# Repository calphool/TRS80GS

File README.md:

# TRS80GS
Storage area for my TRS-80 Model 1 Graphics, Sound, Gaming, and Communication cartidge

My friend's first computer was a 1977 TRS-80 Model 1.  I'm a few years younger than him, so my first computer was a TI-99/4A, 
followed soon after by an Atari 8-bit (800XL I believe).

For some reason my friend kept trying to assert that his *Trash-80* was in some way superior to all home computers of the era, 
and of course this couldn't stand.  I decided to see what all his fussing was about.  I learned some Z80 assembler, 
started hacking a TRS-80 emulator, and eventually got somewhat comfortable with Z80 assembler (I still prefer 6502 assembler).  I 
tried to do some graphics stuff, but *man*, TRS-80 Model 1's *barely* have the ability to do anything you'd call "graphics." 
I did a couple of snow-field type demos, but it looks more like slowly falling bricks on some low-gravity planet than snow.

The TRS-80 uses these goofy ["pseudographics" characters (2 by 3 grids)](https://www.classic-computers.org.nz/system-80/manuals_tm3_page33.jpg), 
and you have to do everything by selecting the right "character" in order to plot these huge blocky pixels.  Your resolution is effectively 128 x 48, and 
it's a pain to work with, because you're actually manipulating a 64 x 16 text grid.  I wrote some assembler code so that I could at least *address* 
the TRS-80 Model 1 screen *as if* it had 128 x 48 resolution, which I've included in this repo (see the snow.asm code, it's the FSETGR routine).

Eventually the day came that I thought "Ok, I'm going to try to write a game for this nasty old thing."  I *really* wanted 
graphics, sound, and a joystick, but alas that wasn't really in the cards for an unmodified TRS-80 Model 1.  So I began 
imagining what it would be like to augment a TRS-80 Model 1 so that it was *at least* as capable as *my* first computer, the 
TI.  I found a couple of dodgy designs for such devices from the era, but they were hand drawn, hard to read, and loaded with 
components that are no longer available.  So, I decided to design my own.

This repo is a gathering place for my work so far.  I've designed a cartridge that will plug into the TRS-80 Model 1 expansion 
port.  It is built around a TMS9118A video display processor (a close relative of the one used in the TI-99/4A and Colecovision).
It also includes two SN76489 sound chips (also from TI-99/4A, but *better* because we have two of them -- six voice harmony baby!)
I've also included a 74LS244 on the bus attached to an Atari 2600 joystick port (DB9), which in theory will give me the 
ability to poll for joystick condition.  That may end up being a bad design, since it's not using any interrupts, but I 
figured I'd start simple and if I need to implement interrupts I'll have to dig into how the TRS-80 deals with them.

**Be Aware**:  ~~I haven't built or tested my card yet (as of March 2018).  So it *probably* doesn't work as is.  We'll see as soon as 
I get finished testing the components individually with an Arduino as a kind of "hardware emulator".  I don't want to risk a 
"40 year old museum piece" while I figure out how to get the "glue" working properly.~~  I *have* now built a working prototype.  
You'll find the eaglecad and such in the rev2 folder (though you'd be better off using the rev4 version).  There's also some source code to test it once you get the board built.  

**Update**:  The photo is of the Rev4 version of this card.  It's fully working, and better than the rev2 and rev3.

Theory of Operation
===================

~~If you examine the *original* schematic for the board, you can see that it's got a bunch of decoding logic, and some SPDT dip switches.  The theory here 
is that I'm attaching the decoding logic to the lower half of [the expansion port's address bus](http://www.classiccmp.org/cpmarchives/trs80/mirrors/kjsl/www.kjsl.com/trs80/mod1intern.html) 
and using the OUT* and IN* pins to decide what we're doing.  In this way, the port address numbers will be adjustable.  
I'm hard wiring bit zero as a toggle bit though, so really you're adjusting the 7 most significant bits, and bit zero toggles 
between related devices or related pins on a device.~~

Strike all that... I pivoted on the design by rev2.  We got rid of silly things like glue logic chips (well, until rev4) and SPDT dip switches, and simply added 
a [CPLD](https://www.microchip.com/wwwproducts/en/ATF22V10C) that manages the address decoding and control signal generation.  The code for the CPLD is now in the repo.  So you 
"adjust" the addresses in code now, not with SPDT dip switches (what was I thinking?)  You program the CPLD with a Stager 4800 programmer, and a very particular version of 
its software (VSpeed 5.0).  Details are in the .PLD file in the repo.  I may eventually add another CPLD and get rid of the couple of glue chips I've got in the rev4 version.  Right now it doesn't 
seem worth it (get rid of two small chips and replace them with a big one?  Sounds like break even right now).

Rev3 includes some addtions.  First, it fixes the sound problem that the rev2 board had so we get both sound chips working (all 6 audio channels and 2 noise channels).  Second, it includes
a [32k SRAM](https://www.mouser.com/ProductDetail/511-M48Z35Y70PC1).  The original expansion system for the TRS-80 used DRAMs, but SRAM actually ends up being much better, especially when you use a non-volatile one like I have.  The Rev3 board 
also cleans up the joystick bodges that I had to do on the Rev2 board.  Rev3 works fully, and I've been building a Pacman game on it.

~~Rev4 is currently (July 2018) being built by our Chinese friends at allpcb.com, and it~~ is an upgraded version of Rev3 with one major improvement -- a [UART](https://en.wikipedia.org/wiki/16550_UART).  I 
~~*should* be~~ am able to connect a [FTDI cable](http://www.ftdichip.com/Products/Cables/USBTTLSerial.htm) via USB from my Mac to this UART and I should be able to transfer binary data back and forth.  
Initially I'll just use it to move my Pacman code back and forth, but in truth with a fully functional UART, I could build a kind of network interface and create something loosely equivalent to a LAN share, 
which would be sort of cool.  In fact, I *could* probably build a SLIP interface and do stuff like surf the web or use FTP from a 40 year old TRS-80 Model 1, but we'll save all that software work for a later date.

The only trouble with having a UART is that now I have *two* interrupts to deal with, so you won't be able to simultaneously use the VPD's interrupts *and* the UART's interrupts.  I've included
a jumper to allow you to switch which one you're working with.  I *suppose* I could add a latch behind an address so that you could tell which interrupt was being invoked, but honestly I 
can't imagine why we need to be both loading data *and* altering the screen at the same time, so Rev4 will use a jumper.  I think I'll start out without coding any interrupt stuff and see what I can get away with
using plain old polling.  It'll be slower, but simpler.  Once I get it working, then I'll look into trickier stuff like interrupt handling in z88dk.

Rev4 is now here and "working" though it took a little bit of hacking to get it up and running.  The original design for 
Rev4 included a separate crystal for the UART (1.8432mhz), but that proved problematic.  It caused the VDP crystal to 
act flaky due to interference.  So, I decided to try removing its crystal and all its support caps and resistors, and just 
drive the XTAL in for the UART from the CPUCLK output of the VDP.  It's the wrong speed (3.5mhz instead of 1.8432mhz), but 
luckily the UART has a divider value that you plug into a register during setup that allows it to use any chip slower than
16mhz.  I coded a couple of little test programs, one for the MAC (the "server") and one for the TRS-80 (the "client").  I
was able to transfer data back and forth, but I'm reaching out to folks on reddit to see if there's a better way to code 
it, since I have an arbitrary 8 millisecond wait on each byte transferred because I don't understand hardware flow control.

TMS9118A
--------
This little VDP chip has an interesting history.  It didn't disappear with the TI-99/4A.  It got used in the Colecovision, and
then its descendants got picked up and used in the MSX computer systems.  Later, it evolved into the graphics and sound chip
used in the Sega Master System and Sega Game Gear.  It has a bank of attached DRAM memory (16k), and you access this memory through
an 8 bit data bus and a few bus flags (MODE, CSR*, and CSW*).  It also has CAS and RAS signals to keep the DRAM running.  So, *technically*, in addition to getting decent graphics and 
sound with this card, we're also giving the TRS-80 Model 1 an additional 16k of RAM, though it's only accessible through a 
tiny keyhole of two IO ports, and much of it is used up by the VDP chip itself (depending on what mode you set it to).

~~At the time of this writing (March 2018), I've managed to bodge up a working TMS9118A on a breadboard, and drive it with an 
Arduino.  I've uploaded the Arduino code for that, and an incredibly frightening breadboard photo that looks like something out of 
the movie Aliens.  The code doesn't do anything too spectacular, but just changes the background color, which means that 
I've successfully managed to figure out how to drive the WRITE side of the chip (writing to what the VDP calls "control 
registers", which are how you set up almost everything in the VDP).  I've also included a small video showing it doing that.~~

We're way past that stage now.  The TMS9118 works like a dream, and I've been building a Pacman clone against it, using the z88dk C compiler.  So far I'm fitting inside my nice 32k RAM addition
just fine.  There's a lot of fluff in my code, and I'm pretty sure I could get it crammed down at least 25% if I worked at it.  Right now I've got an animated pacman that can move around inside
the maze, and I've got the intro music working.  Ghosts and dots coming soon....

SN76489
-------
~~I haven't done much with the sound chips yet, but hopefully they'll be a bit easier to manage than the VDP.  Bit 0 of the 
address bus will toggle between them.  Stereo baby!~~

Sound didn't work quite right in the rev2 board design.  There's a "Ready" line on the SN76489 that needed to be tied to the WAIT line on the TRS-80 interface.  Why?  Because the SN76489 doesn't
like receiving a second byte when it's still processing the first one.  I *could* write all my code to put a delay inbetween each byte send, but that's kind of lame and non-deterministic.  The
WAIT line was originally conceived so that the TRS-80 could interface to "slow" peripherals, and although the sound chip isn't *super* slow, it seemed the way to go was to tie that READY line 
to it.  Unfortunately on the rev2 board that meant that I couldn't use *both* sound chips, because I didn't have a free OR gate anywhere to run the two Ready lines through.  So, I pulled one of them
and just wired the other one up on the rev2 board.  It worked as expected.  This has all been cleaned up in the rev3 and rev4 boards.

74LS244
-------
This is managing the joystick switches.  It takes 5 switches to handle up, down, left, right, and trigger.  ~~I don't have any
kind of debounce circuit in there, so I'm guessing that'll be a problem.  We'll see when we get there.~~

Joystick circuits worked more or less flawlessly, though I had stuff wired backward on the PCB for rev2.  I had to bodge some jumper wires to get them working because of that, but that's all cleaned 
up in Rev3 and Rev4.  I originally was toying with the idea of building some kind of one-way parallel interface that used the joystick ports, but the more I thought about it the less I liked it and
decided to add the UART instead.

ExtVid
------
I don't really know if I'll do this, but it's sort of an intriguing idea.  Apparently the TMS9118A has a "video input" pin, 
believe it or not.  In principle at least, I could feed the video out of the TRS-80 to the video-input of the TMS9118A, and it
will *combine* the video together, with the TRS-80's video feed at the bottom of the stack of planes that the TMS9118A creates (which, 
by the way is how it manages sprites -- 32 of them as separate planes stacked on top of each other).  If I do this, and it 
works, it could create some interesting possibilities.  You'd still have the "feel" of a TRS-80 Model 1 with its nasty, clunky
pseudographics, but then you could overlay color and sprites over the top of it.  I guess we'll see when we get there.  The 
current (March 2018) schematics don't implement this idea.

(July 2018) I haven't done anything with ExtVid yet.  I've come to realize that it's unlikely to just work out of the box, because the 
RESET line on the TMS9118A does double duty as some kind of video sync signal.  So I'd probably have to come up with a sync separator 
circuit for the ExtVid line, then amplify that signal up to whatever ungodly voltage causes the RESET to act like a SYNC signal.  I probably should just
hook up a video signal to see how bad it tears as it moves down the screen -- maybe it's still usable without all that extra circuitry -- just haven't 
tried it yet.

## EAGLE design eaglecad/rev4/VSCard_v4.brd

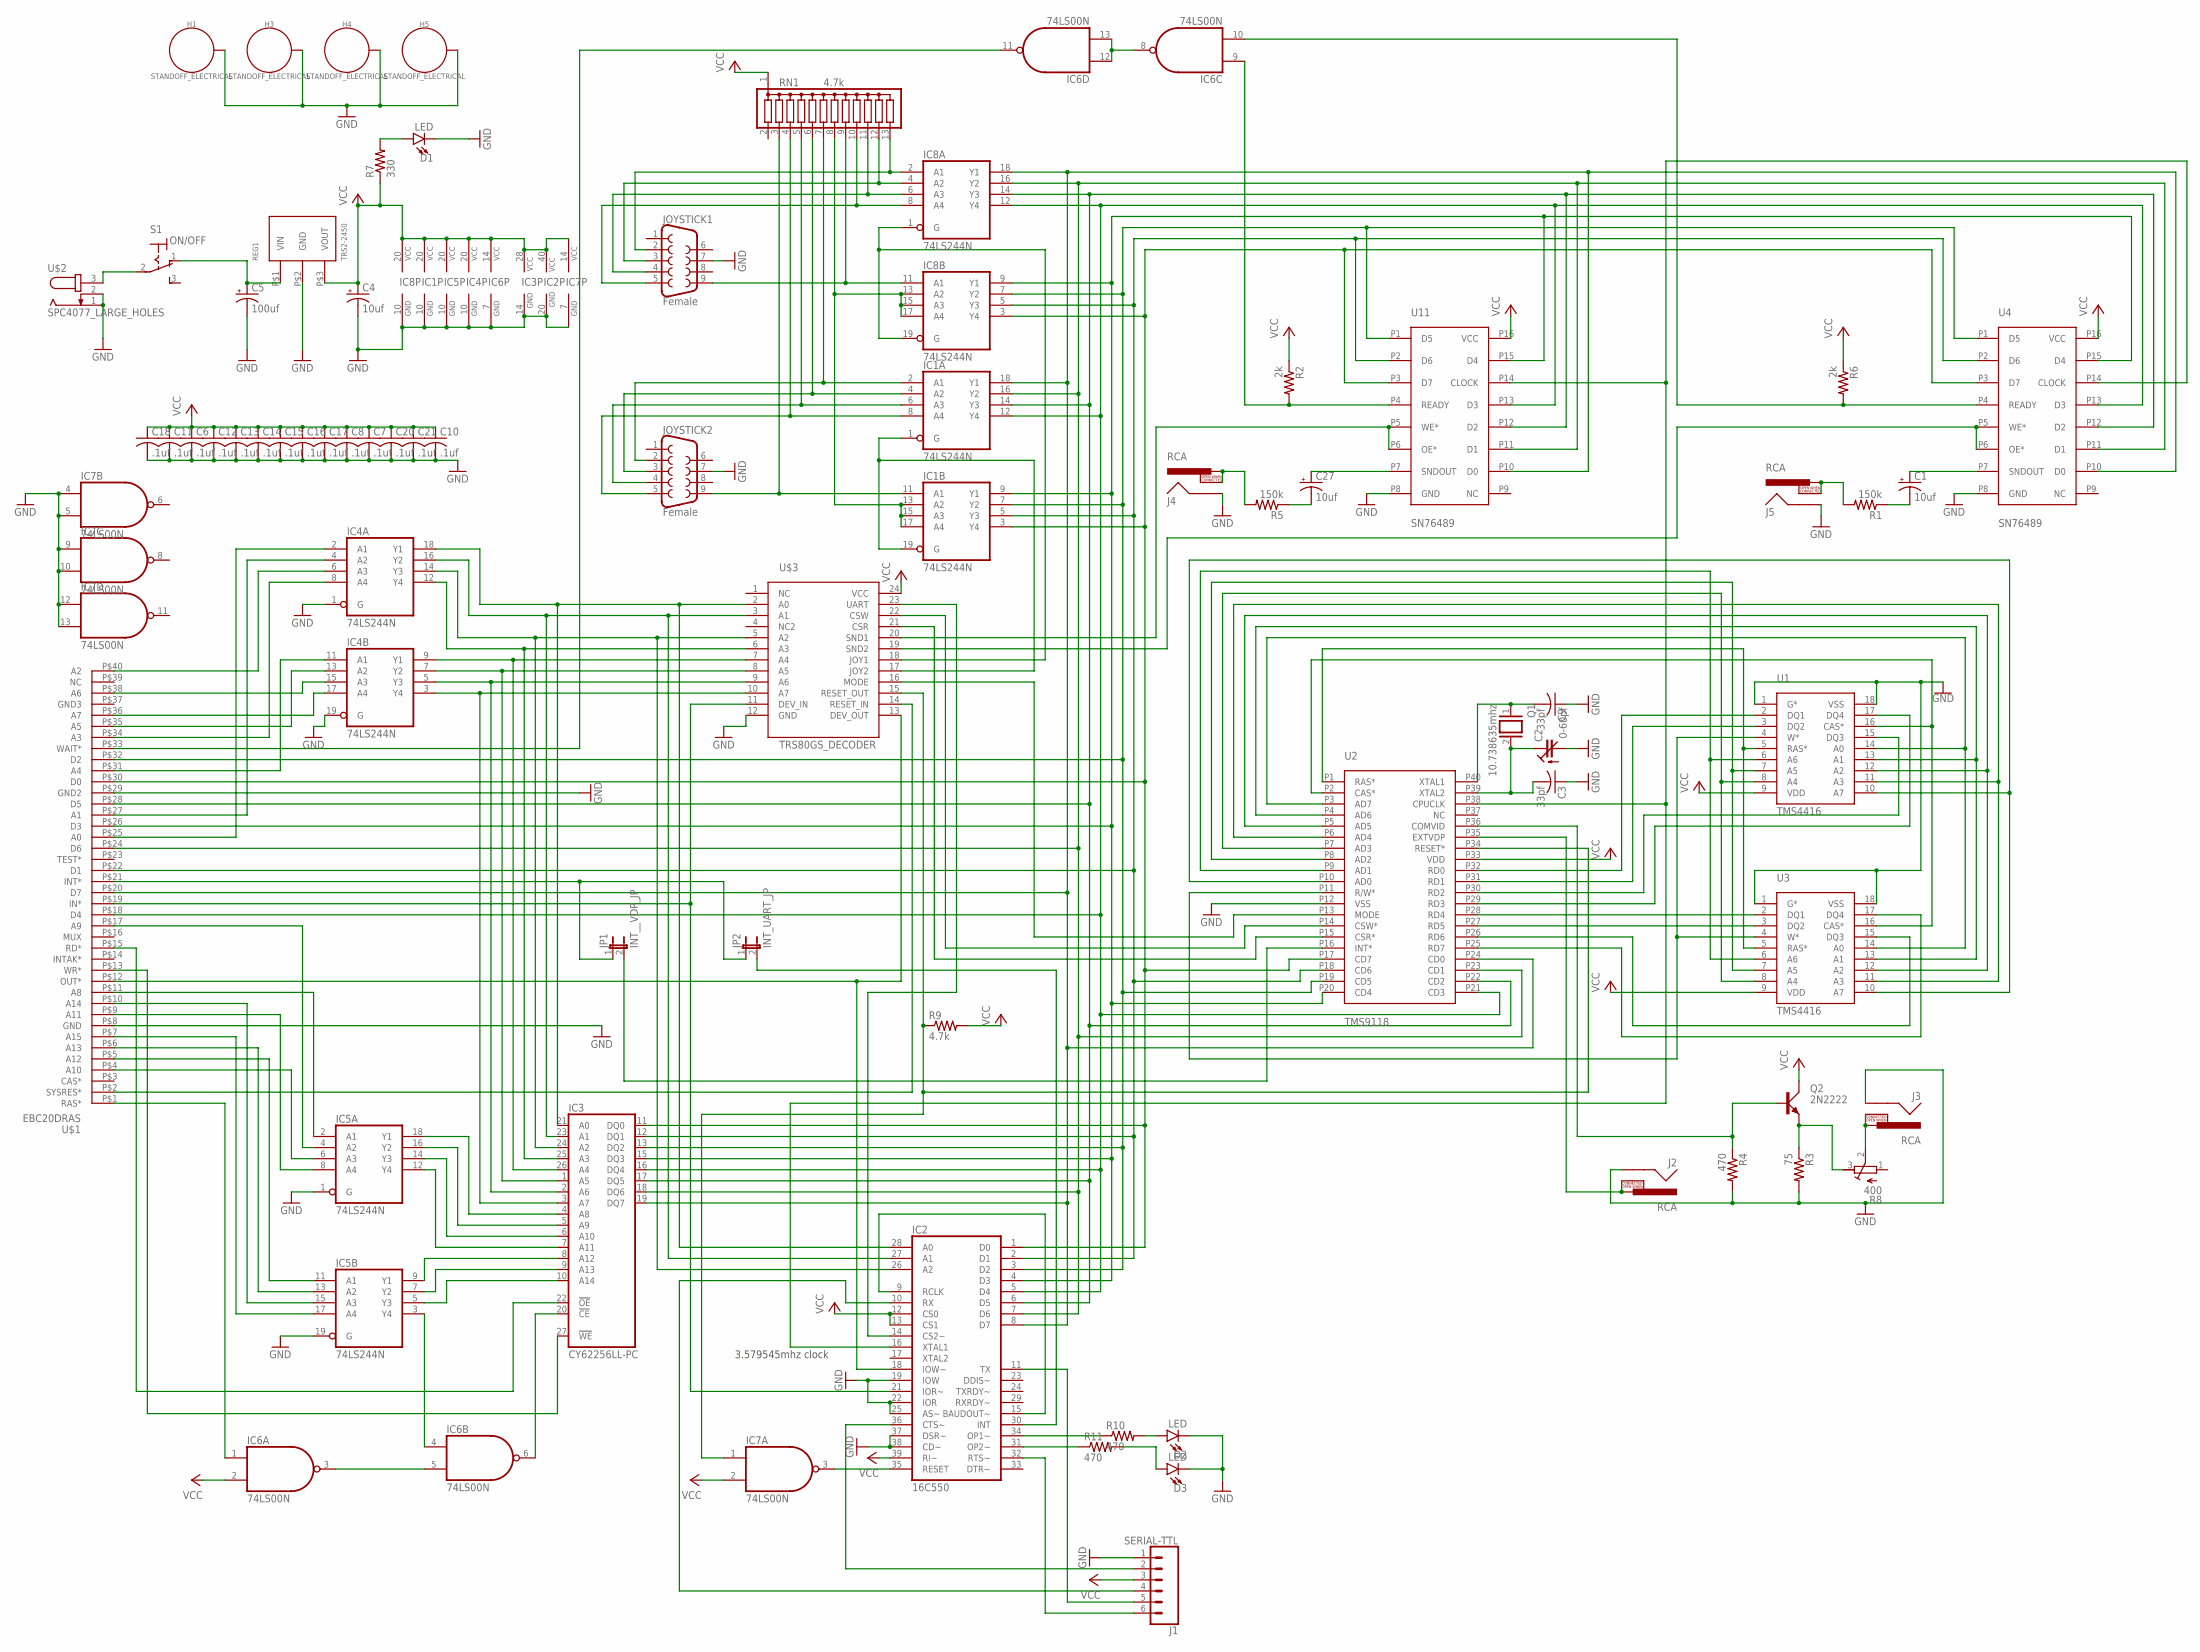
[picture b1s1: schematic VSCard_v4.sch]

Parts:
C1, C27: 10uf; E2,5-6
C2: 0-60pf; CTRIM3050.504
C3, C9: 33pf; C050-050X075
C4: 10uf; E2,5-5
C5: 100uf; E3,5-10
C6, C7, C8, C10, C11, C12, C13, C14, C15, C16, C17, C18, C20, C21: .1uf; C025-025X050
D1, D2, D3: LED; LED_3MM
H1, H3, H4, H5: STANDOFF_ELECTRICAL; STANDOFF-ELECTRICAL
IC1, IC4, IC5, IC8: 74LS244N; DIL20
IC2: 16C550; DIL40
IC3: CY62256LL-PC; DIL28-6
IC6, IC7: 74LS00N; DIL14
J1: SERIAL-TTL; 1X06_NO_SILK
J2, J3, J4, J5: RCA
JOYSTICK1, JOYSTICK2: Female; DB9
JP1: INT__VDP_JP; JP1
JP2: INT_UART_JP; JP1
Q1: 10.738635mhz; QS
Q2: 2N2222; TO18A
R1, R5: 150k; 0207/2V
R2, R6: 2k; 0207/2V
R3: 75; 0207/2V
R4, R10, R11: 470; 0207/2V
R7: 330; 0309V
R8: 400; RTRIM64W
R9: 4.7k; 0207/2V
REG1: TRS2-2450; TRACON_REG
RN1: 4.7k; SIL13
S1: ON/OFF; 320-916
U1, U3: TMS4416; DIP18
U2: TMS9118; DIP40_MCU
U4, U11: SN76489; DIP16
U$1: EBC20DRAS
U$2: SPC4077_LARGE_HOLES; SPC4077
U$3: TRS80GS_DECODER; DIP24SKI

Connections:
A0_BUFFERED: IC2.28 (A0), IC3.21 (A0), IC4.18 (Y1), U$3.2 (A0)
A0_RAW: IC4.2 (A1), U$1.P$25 (A0)
A1_BUFFERED: IC2.27 (A1), IC3.23 (A1), IC4.16 (Y2), U$3.3 (A1)
A1_RAW: IC4.4 (A2), U$1.P$27 (A1)
A2_BUFFERED: IC2.26 (A2), IC3.24 (A2), IC4.14 (Y3), U$3.5 (A2)
A2_RAW: IC4.6 (A3), U$1.P$40 (A2)
A3_BUFFERED: IC3.25 (A3), IC4.12 (Y4), U$3.6 (A3)
A3_RAW: IC4.8 (A4), U$1.P$34 (A3)
A4_BUFFERED: IC3.26 (A4), IC4.9 (Y1), U$3.7 (A4)
A4_RAW: IC4.11 (A1), U$1.P$31 (A4)
A5_BUFFERED: IC3.1 (A5), IC4.7 (Y2), U$3.8 (A5)
A5_RAW: IC4.13 (A2), U$1.P$35 (A5)
A6_BUFFERED: IC3.2 (A6), IC4.5 (Y3), U$3.9 (A6)
A6_RAW: IC4.15 (A3), U$1.P$38 (A6)
A7_BUFFERED: IC3.3 (A7), IC4.3 (Y4), U$3.10 (A7)
A7_RAW: IC4.17 (A4), U$1.P$36 (A7)
A8_BUFFERED: IC3.4 (A8), IC5.18 (Y1)
A8_RAW: IC5.2 (A1), U$1.P$11 (A8)
A9_BUFFERED: IC3.5 (A9), IC5.16 (Y2)
A9_RAW: IC5.4 (A2), U$1.P$17 (A9)
A10_BUFFERED: IC3.6 (A10), IC5.14 (Y3)
A10_RAW: IC5.6 (A3), U$1.P$4 (A10)
A11_BUFFERED: IC3.7 (A11), IC5.12 (Y4)
A11_RAW: IC5.8 (A4), U$1.P$9 (A11)
A12_BUFFERED: IC3.8 (A12), IC5.9 (Y1)
A12_RAW: IC5.11 (A1), U$1.P$5 (A12)
A13_BUFFERED: IC3.9 (A13), IC5.7 (Y2)
A13_RAW: IC5.13 (A2), U$1.P$6 (A13)
A14_BUFFERED: IC3.10 (A14), IC5.5 (Y3)
A14_RAW: IC5.15 (A3), U$1.P$10 (A14)
A15_BUFFERED: IC5.3 (Y4), IC6.4 (I0)
A15_RAW: IC5.17 (A4), U$1.P$7 (A15)
COMVID: Q2.B, R4.1, U2.P36 (COMVID)
COMVID-OUT: Q2.E, R3.1, R8.3 (E)
CTS*: IC2.36 (CTS~), J1.2
D0: IC1.3 (Y4), IC2.1 (D0), IC3.11 (DQ0), IC8.3 (Y4), U2.P17 (CD7), U4.P3 (D7), U11.P3 (D7), U$1.P$30 (D0)
D1: IC1.5 (Y3), IC2.2 (D1), IC3.12 (DQ1), IC8.5 (Y3), U2.P18 (CD6), U4.P2 (D6), U11.P2 (D6), U$1.P$22 (D1)
D2: IC1.7 (Y2), IC2.3 (D2), IC3.13 (DQ2), IC8.7 (Y2), U2.P19 (CD5), U4.P1 (D5), U11.P1 (D5), U$1.P$32 (D2)
D3: IC1.9 (Y1), IC2.4 (D3), IC3.15 (DQ3), IC8.9 (Y1), U2.P20 (CD4), U4.P15 (D4), U11.P15 (D4), U$1.P$26 (D3)
D4: IC1.12 (Y4), IC2.5 (D4), IC3.16 (DQ4), IC8.12 (Y4), U2.P21 (CD3), U4.P13 (D3), U11.P13 (D3), U$1.P$18 (D4)
D5: IC1.14 (Y3), IC2.6 (D5), IC3.17 (DQ5), IC8.14 (Y3), U2.P22 (CD2), U4.P12 (D2), U11.P12 (D2), U$1.P$28 (D5)
D6: IC1.16 (Y2), IC2.7 (D6), IC3.18 (DQ6), IC8.16 (Y2), U2.P23 (CD1), U4.P11 (D1), U11.P11 (D1), U$1.P$24 (D6)
D7: IC1.18 (Y1), IC2.8 (D7), IC3.19 (DQ7), IC8.18 (Y1), U2.P24 (CD0), U4.P10 (D0), U11.P10 (D0), U$1.P$20 (D7)
DOWN: IC8.4 (A2), JOYSTICK1.3, RN1.12
DOWN1: IC1.4 (A2), JOYSTICK2.3, RN1.6
GND: C2.2 (A), C3.1, C4.-, C5.-, C6.2, C7.2, C8.2, C9.1, C10.2, C11.2, C12.2, C13.2, C14.2, C15.2, C16.2, C17.2, C18.2, C20.2, C21.2, D1.K (C), D2.K (C), D3.K (C), H1.P1, H3.P1, H4.P1, H5.P1, IC1.10 (GND), IC2.19 (IOW), IC2.20 (GND), IC2.22 (IOR), IC2.25 (AS~), IC2.37 (DSR~), IC2.38 (CD~), IC3.14 (GND), IC4.1 (G), IC4.10 (GND), IC4.19 (G), IC5.1 (G), IC5.10 (GND), IC5.19 (G), IC6.7 (GND), IC7.4 (I0), IC7.5 (I1), IC7.7 (GND), IC7.9 (I0), IC7.10 (I1), IC7.12 (I0), IC7.13 (I1), IC8.10 (GND), J1.1, J2.SHELL, J3.SHELL, J4.SHELL, J5.SHELL, JOYSTICK1.7, JOYSTICK2.7, R3.2, R4.2, REG1.P$2 (GND), U1.1 (G*), U1.18 (VSS), U2.P12 (VSS), U3.1 (G*), U3.18 (VSS), U4.P8 (GND), U11.P8 (GND), U$1.P$8 (GND), U$1.P$29 (GND2), U$2.1, U$2.2, U$3.12 (GND)
IN*: IC2.21 (IOR~), U$1.P$19 (IN*), U$3.11 (DEV_IN)
INT*: JP1.1, JP2.1, U$1.P$21 (INT*)
JOY1_IN_ENABLE_N: IC8.1 (G), IC8.19 (G), U$3.18 (JOY1)
JOY1_IN_ENABLE_N1: IC1.1 (G), IC1.19 (G), U$3.17 (JOY2)
LEFT: IC8.6 (A3), JOYSTICK1.4, RN1.11
LEFT1: IC1.6 (A3), JOYSTICK2.4, RN1.5
unnamed: J4.PIN, J4.SWITCH, R5.2
unnamed: S1.2, U$2.3
unnamed: JP1.2, U2.P16 (INT*)
unnamed: J3.PIN, J3.SWITCH, R8.2 (S)
unnamed: IC2.30 (INT), JP2.2
unnamed: IC2.14 (CS2~), U$3.23 (UART)
unnamed: IC2.35 (RESET), IC7.3 (O)
unnamed: IC2.34 (OP1~), R10.1
unnamed: IC2.31 (OP2~), R11.1
unnamed: D2.A, R10.2
unnamed: D3.A, R11.2
unnamed: U2.P14 (CSW*), U$3.22 (CSW)
unnamed: U2.P15 (CSR*), U$3.21 (CSR)
unnamed: C2.1 (E), C3.2, Q1.2, U2.P39 (XTAL2)
unnamed: J2.PIN, J2.SWITCH, U2.P35 (EXTVDP)
unnamed: U1.5 (RAS*), U2.P1 (RAS*), U3.5 (RAS*)
unnamed: D1.A, R7.2
unnamed: U1.16 (CAS*), U2.P2 (CAS*), U3.16 (CAS*)
unnamed: IC2.9 (RCLK), IC2.15 (BAUDOUT~)
unnamed: J5.PIN, J5.SWITCH, R1.2
unnamed: IC6.1 (I0), U$1.P$1 (RAS*)
unnamed: IC6.3 (O), IC6.5 (I1)
unnamed: IC3.20 (!CE), IC6.6 (O)
unnamed: IC6.8 (O), IC6.12 (I0), IC6.13 (I1)
unnamed: C27.-, R5.1
unnamed: C1.-, R1.1
unnamed: IC1.13 (A2), IC1.15 (A3), IC1.17 (A4), IC8.13 (A2), IC8.15 (A3), IC8.17 (A4), RN1.8
OUT*: IC2.18 (IOW~), U$1.P$12 (OUT*), U$3.13 (DEV_OUT)
RD_: IC3.22 (!OE), U$1.P$15 (RD*)
RIGHT: IC8.8 (A4), JOYSTICK1.5, RN1.10
RIGHT1: IC1.8 (A4), JOYSTICK2.5, RN1.4
RTS*: IC2.32 (RTS~), J1.6
SIN: IC2.10 (RX), J1.4
SN76489-CLOCK: IC2.16 (XTAL1), U2.P38 (CPUCLK), U4.P14 (CLOCK), U11.P14 (CLOCK)
SND1_ENABLE_N: U11.P5 (WE*), U11.P6 (OE*), U$3.20 (SND1)
SND1_READY: IC6.9 (I0), R2.2, U11.P4 (READY)
SND2_ENABLE_N: U4.P5 (WE*), U4.P6 (OE*), U$3.19 (SND2)
SND2_READY: IC6.10 (I1), R6.2, U4.P4 (READY)
SNDOUT1: C27.+, U11.P7 (SNDOUT)
SNDOUT2: C1.+, U4.P7 (SNDOUT)
SOUT: IC2.11 (TX), J1.5
SYSRESET*: U$1.P$2 (SYSRES*), U$3.14 (RESET_IN)
TMS9118_RW(*)_TMS4416_W(*): U1.4 (W*), U2.P11 (R/W*), U3.4 (W*)
TMS9918_AD0-TMS4416_A7: U1.10 (A7), U2.P10 (AD0), U3.10 (A7)
TMS9918_AD1-TMS4416_A6: U1.6 (A6), U2.P9 (AD1), U3.6 (A6)
TMS9918_AD2-TMS4416_A5: U1.7 (A5), U2.P8 (AD2), U3.7 (A5)
TMS9918_AD3-TMS4416_A4: U1.8 (A4), U2.P7 (AD3), U3.8 (A4)
TMS9918_AD4-TMS4416_A3: U1.11 (A3), U2.P6 (AD4), U3.11 (A3)
TMS9918_AD5-TMS4416_A2: U1.12 (A2), U2.P5 (AD5), U3.12 (A2)
TMS9918_AD6-TMS4416_A1: U1.13 (A1), U2.P4 (AD6), U3.13 (A1)
TMS9918_AD7-TMS4416_A0: U1.14 (A0), U2.P3 (AD7), U3.14 (A0)
TRIGGER: IC8.11 (A1), JOYSTICK1.9, RN1.9
TRIGGER1: IC1.11 (A1), JOYSTICK2.9, RN1.3
UP: IC8.2 (A1), JOYSTICK1.2, RN1.13
UP1: IC1.2 (A1), JOYSTICK2.2, RN1.7
VCC: C4.+, C6.1, C7.1, C8.1, C10.1, C11.1, C12.1, C13.1, C14.1, C15.1, C16.1, C17.1, C18.1, C20.1, C21.1, IC1.20 (VCC), IC2.12 (CS0), IC2.13 (CS1), IC2.39 (RI~), IC2.40 (VCC), IC3.28 (VCC), IC4.20 (VCC), IC5.20 (VCC), IC6.2 (I1), IC6.14 (VCC), IC7.2 (I1), IC7.14 (VCC), IC8.20 (VCC), J1.3, Q2.C, R2.1, R6.1, R7.1, R9.2, REG1.P$3 (VOUT), RN1.1, U1.9 (VDD), U2.P33 (VDD), U3.9 (VDD), U4.P16 (VCC), U11.P16 (VCC), U$3.24 (VCC)
VDP-RD0: U1.2 (DQ1), U2.P32 (RD0)
VDP-RD1: U1.3 (DQ2), U2.P31 (RD1)
VDP-RD2: U1.15 (DQ3), U2.P30 (RD2)
VDP-RD3: U1.17 (DQ4), U2.P29 (RD3)
VDP-RD4: U2.P28 (RD4), U3.2 (DQ1)
VDP-RD5: U2.P27 (RD5), U3.3 (DQ2)
VDP-RD6: U2.P26 (RD6), U3.15 (DQ3)
VDP-RD7: U2.P25 (RD7), U3.17 (DQ4)
VDP_MODE: U2.P13 (MODE), U$3.16 (MODE)
VID_RESET*: IC7.1 (I0), R9.1, U2.P34 (RESET*), U$3.15 (RESET_OUT)
VOLTAGE-IN: C5.+, REG1.P$1 (VIN), S1.1 (O)
WAIT*: IC6.11 (O), U$1.P$33 (WAIT*)
WR_: IC3.27 (!WE), U$1.P$13 (WR*)
XTAL1: C9.2, Q1.1, U2.P40 (XTAL1)

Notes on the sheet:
3.579545mhz clock

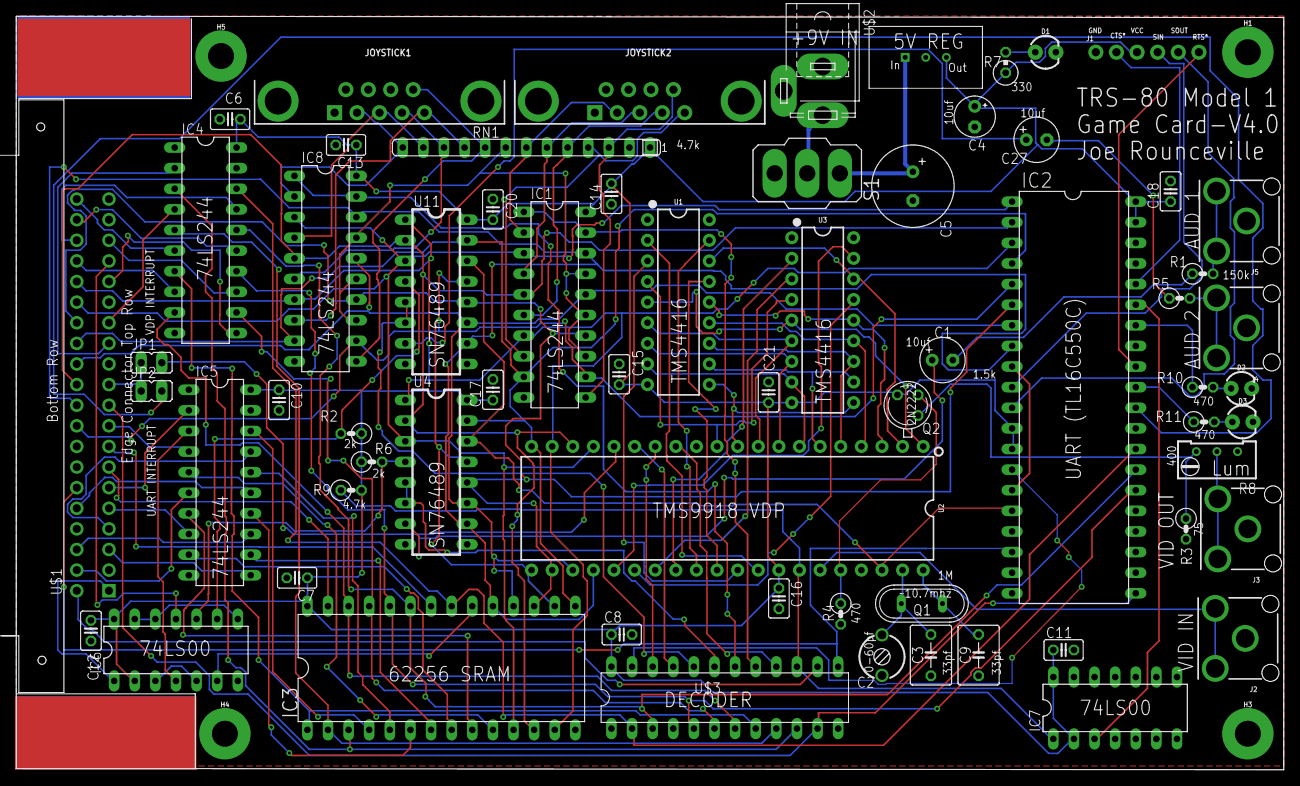
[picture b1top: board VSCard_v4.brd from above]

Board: 2 copper layers, 156.2 x 92.9 mm, 69 parts (0 on the bottom side), 122 nets.

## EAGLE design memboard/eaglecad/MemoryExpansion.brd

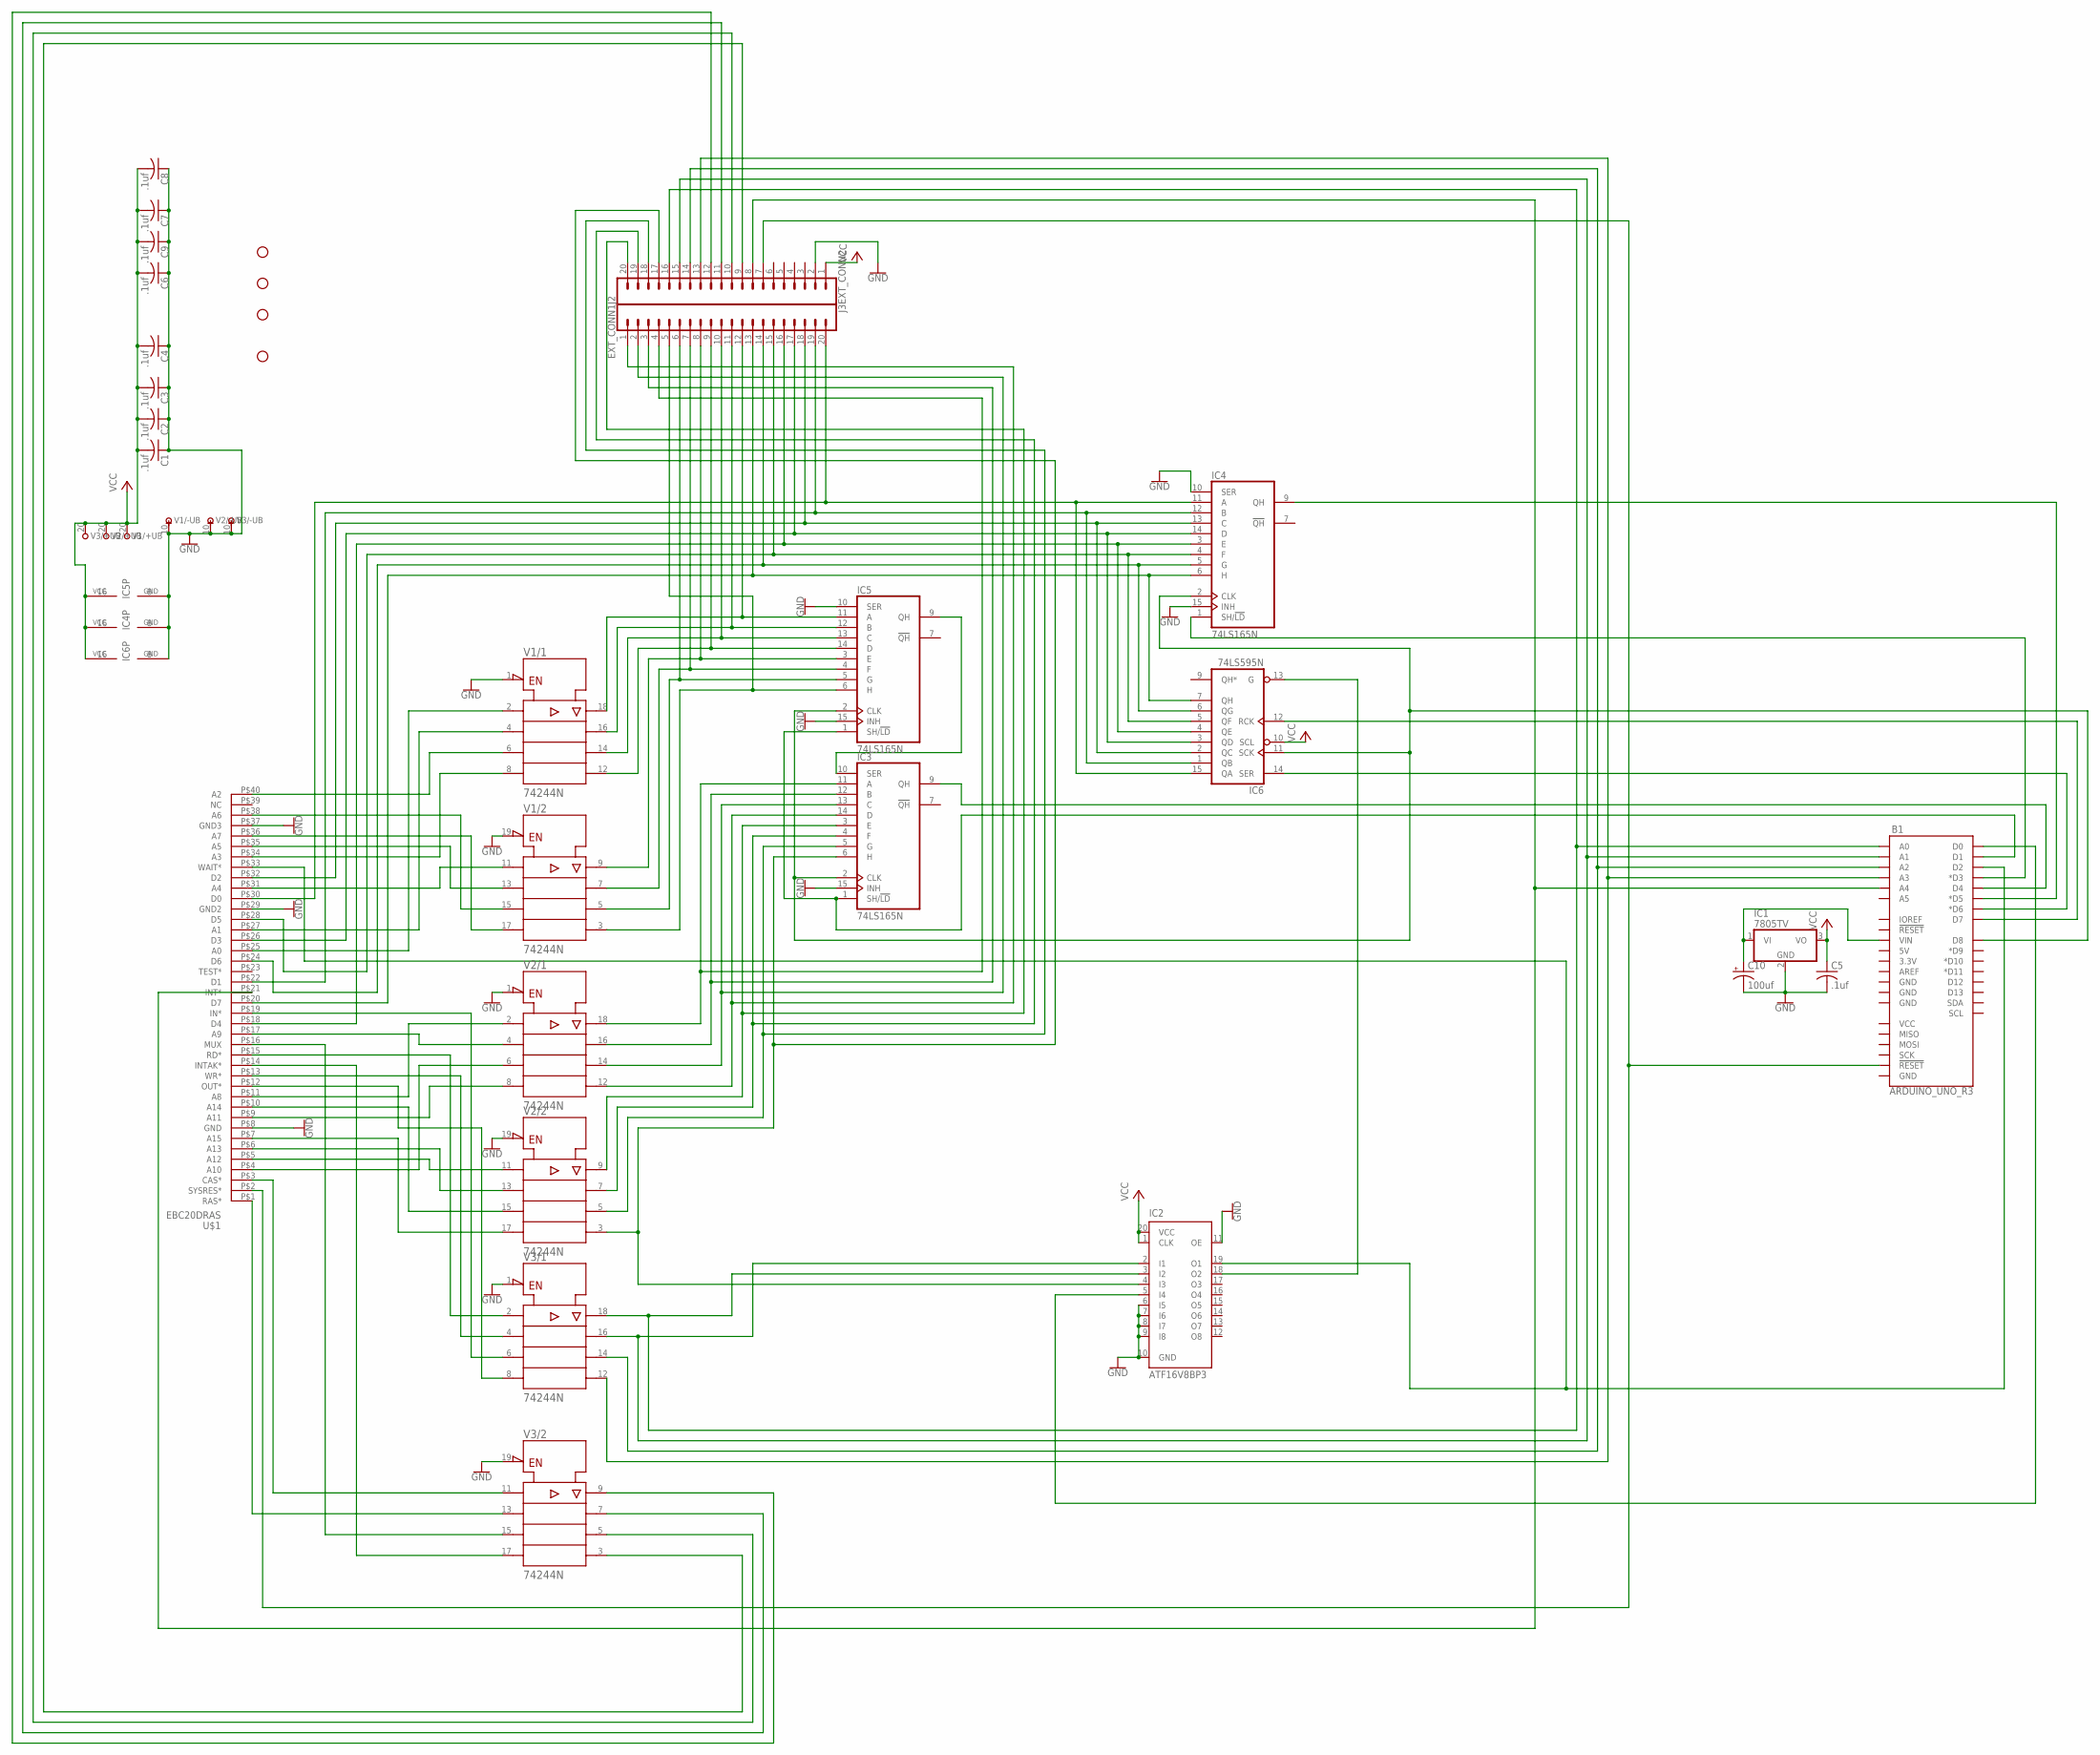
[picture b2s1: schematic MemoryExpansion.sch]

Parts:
B1: ARDUINO_UNO_R3; ARDUINO_R3
C1, C2, C3, C4, C5, C6, C7, C8, C9: .1uf; C025-024X044
C10: 100uf; E2-5
H1, H2, H3, H4: STAND-OFF
IC1: 7805TV; TO220V
IC2: ATF16V8BP3; DIL20
IC3, IC4, IC5: 74LS165N; DIL16
IC6: 74LS595N; DIL16
J2: EXT_CONN2; 1X20
J3: EXT_CONN1; 1X20
U$1: EBC20DRAS
V1, V2, V3: 74244N; DIL20

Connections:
A_12_NET: U$1.P$5 (A12), V2.11 (A1)
A_13_NET: U$1.P$6 (A13), V2.13 (A2)
A_14_NET: U$1.P$10 (A14), V2.15 (A3)
A_15_NET: U$1.P$7 (A15), V2.17 (A4)
BUF_A_12_NET: IC3.3 (E), J2.20, V2.9 (Y1)
BUF_A_13_NET: IC3.4 (F), J2.19, V2.7 (Y2)
BUF_A_14_NET: IC3.5 (G), J2.18, V2.5 (Y3)
BUF_A_15_NET: IC2.4 (I3), IC3.6 (H), J2.17, V2.3 (Y4)
BUF_IN_N_NET: B1.A2, J2.14, V3.14 (Y3)
BUF_OUT_N_NET: B1.A3, J2.13, V3.12 (Y4)
BUF_RD_N_NET: B1.A0, IC2.3 (I2), J2.16, V3.18 (Y1)
BUF_WR_N_NET: B1.A1, IC2.2 (I1), J2.15, V3.16 (Y2)
DECODE_ENABLE: B1.D0, IC2.5 (I4)
GND: C1.1, C2.1, C3.1, C4.1, C5.2, C6.1, C7.1, C8.1, C9.1, C10.-, IC1.2 (GND), IC2.6 (I5), IC2.7 (I6), IC2.8 (I7), IC2.9 (I8), IC2.10 (GND), IC2.11 (OE), IC3.8 (GND), IC3.15 (INH), IC4.8 (GND), IC4.10 (SER), IC4.15 (INH), IC5.8 (GND), IC5.10 (SER), IC5.15 (INH), IC6.8 (GND), J2.2, U$1.P$8 (GND), U$1.P$29 (GND2), U$1.P$37 (GND3), V1.1 (!G), V1.10 (-UB), V1.19 (!G), V2.1 (!G), V2.10 (-UB), V2.19 (!G), V3.1 (!G), V3.10 (-UB), V3.19 (!G)
IN_N_NET: U$1.P$19 (IN*), V3.6 (A3)
unnamed: U$1.P$25 (A0), V1.2 (A1)
unnamed: U$1.P$27 (A1), V1.4 (A2)
unnamed: U$1.P$40 (A2), V1.6 (A3)
unnamed: U$1.P$34 (A3), V1.8 (A4)
unnamed: U$1.P$31 (A4), V1.11 (A1)
unnamed: U$1.P$35 (A5), V1.13 (A2)
unnamed: U$1.P$38 (A6), V1.15 (A3)
unnamed: U$1.P$36 (A7), V1.17 (A4)
unnamed: U$1.P$11 (A8), V2.2 (A1)
unnamed: U$1.P$17 (A9), V2.4 (A2)
unnamed: U$1.P$4 (A10), V2.6 (A3)
unnamed: U$1.P$9 (A11), V2.8 (A4)
unnamed: B1.VIN, C10.+, IC1.1 (VI)
unnamed: B1.D6 (*D6), IC6.14 (SER)
unnamed: B1.D7, IC6.12 (RCK)
unnamed: U$1.P$3 (CAS*), V3.11 (A1)
unnamed: IC3.10 (SER), IC5.9 (QH)
unnamed: B1.D8, IC3.2 (CLK), IC4.2 (CLK), IC5.2 (CLK), IC6.11 (SCK)
unnamed: IC5.11 (A), J3.12, V1.18 (Y1)
unnamed: B1.D1, IC3.1 (SH/!LD), IC5.1 (SH/!LD)
unnamed: B1.D3 (*D3), IC4.1 (SH/!LD)
unnamed: B1.D4, IC3.9 (QH)
unnamed: B1.D5 (*D5), IC4.9 (QH)
unnamed: B1.A4, J2.8, U$1.P$21 (INT*)
unnamed: U$1.P$1 (RAS*), V3.13 (A2)
unnamed: U$1.P$16 (MUX), V3.15 (A3)
unnamed: IC5.12 (B), J3.11, V1.16 (Y2)
unnamed: IC5.13 (C), J3.10, V1.14 (Y3)
unnamed: IC5.14 (D), J3.9, V1.12 (Y4)
unnamed: IC5.3 (E), J3.8, V1.9 (Y1)
unnamed: IC5.4 (F), J3.7, V1.7 (Y2)
unnamed: IC5.5 (G), J3.6, V1.5 (Y3)
unnamed: IC5.6 (H), J3.5, V1.3 (Y4)
unnamed: U$1.P$14 (INTAK*), V3.17 (A4)
unnamed: IC3.11 (A), J3.4, V2.18 (Y1)
unnamed: IC3.12 (B), J3.3, V2.16 (Y2)
unnamed: IC3.13 (C), J3.2, V2.14 (Y3)
unnamed: IC3.14 (D), J3.1, V2.12 (Y4)
unnamed: B1.RESET@2 (!RESET!), J2.7, U$1.P$2 (SYSRES*)
unnamed: J2.12, V3.9 (Y1)
unnamed: J2.11, V3.7 (Y2)
unnamed: J2.10, V3.5 (Y3)
unnamed: IC4.11 (A), IC6.15 (QA), J3.20, U$1.P$30 (D0)
unnamed: IC4.12 (B), IC6.1 (QB), J3.19, U$1.P$22 (D1)
unnamed: IC4.13 (C), IC6.2 (QC), J3.18, U$1.P$32 (D2)
unnamed: IC4.14 (D), IC6.3 (QD), J3.17, U$1.P$26 (D3)
unnamed: IC4.3 (E), IC6.4 (QE), J3.16, U$1.P$18 (D4)
unnamed: IC4.4 (F), IC6.5 (QF), J3.15, U$1.P$28 (D5)
unnamed: IC4.5 (G), IC6.6 (QG), J3.14, U$1.P$24 (D6)
unnamed: IC4.6 (H), IC6.7 (QH), J3.13, U$1.P$20 (D7)
unnamed: J2.9, V3.3 (Y4)
OUT_N_NET: U$1.P$12 (OUT*), V3.8 (A4)
RDH_N: IC2.18 (O2), IC6.13 (G)
RD_N_NET: U$1.P$15 (RD*), V3.2 (A1)
VCC: C1.2, C2.2, C3.2, C4.2, C5.1, C6.2, C7.2, C8.2, C9.2, IC1.3 (VO), IC2.1 (CLK), IC2.20 (VCC), IC3.16 (VCC), IC4.16 (VCC), IC5.16 (VCC), IC6.10 (SCL), IC6.16 (VCC), J2.1, V1.20 (+UB), V2.20 (+UB), V3.20 (+UB)
WAIT/: B1.D2, IC2.19 (O1), U$1.P$33 (WAIT*)
WR_N_NET: U$1.P$13 (WR*), V3.4 (A2)

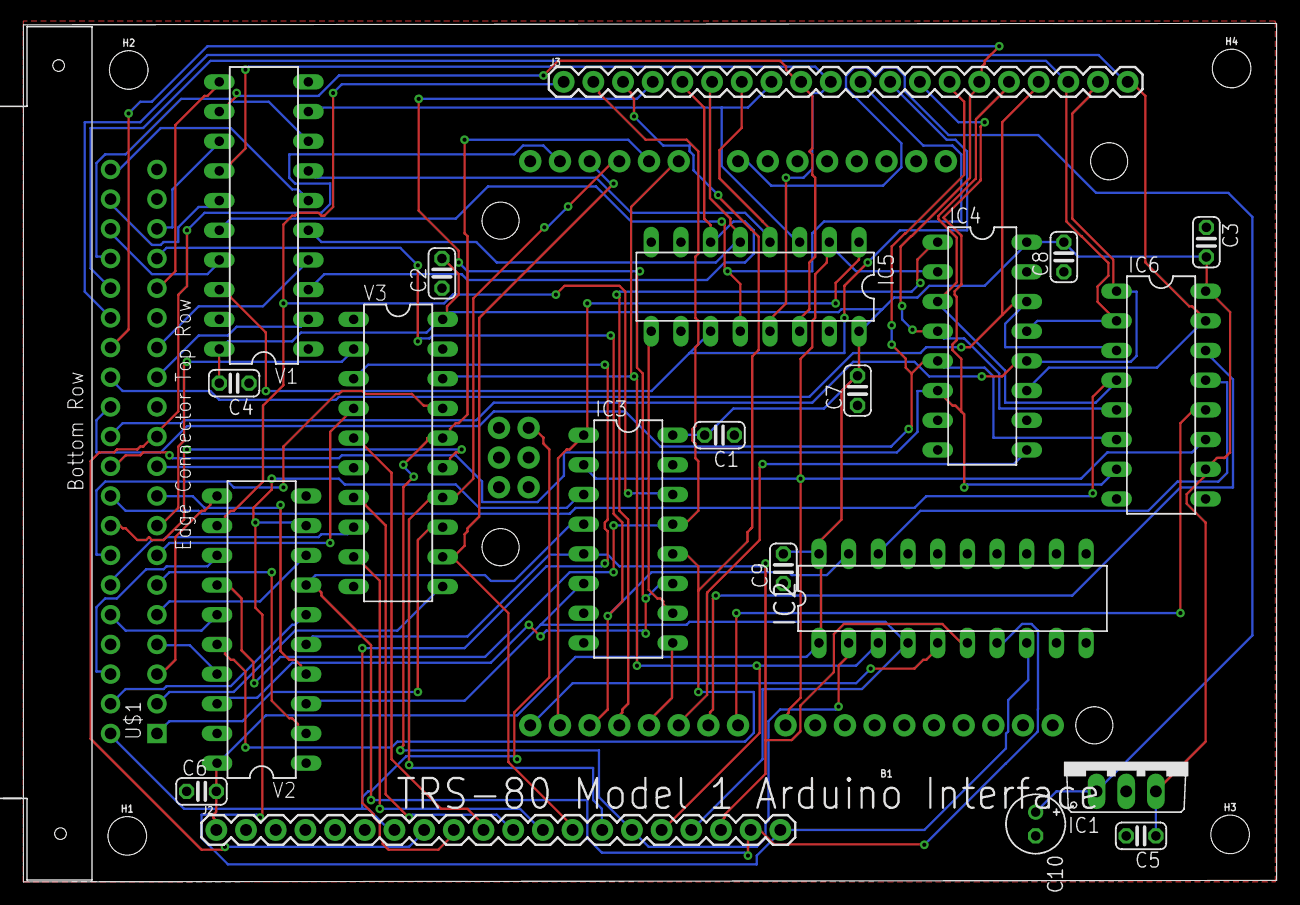
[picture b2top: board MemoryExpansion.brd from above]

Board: 2 copper layers, 107.2 x 73.5 mm, 27 parts (0 on the bottom side), 72 nets.

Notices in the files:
parts and their libraries:
SparkFun-Hardware: Licensing: Creative Commons ShareAlike 4.0 International - https://creativecommons.org/licenses/by-sa/4.0
